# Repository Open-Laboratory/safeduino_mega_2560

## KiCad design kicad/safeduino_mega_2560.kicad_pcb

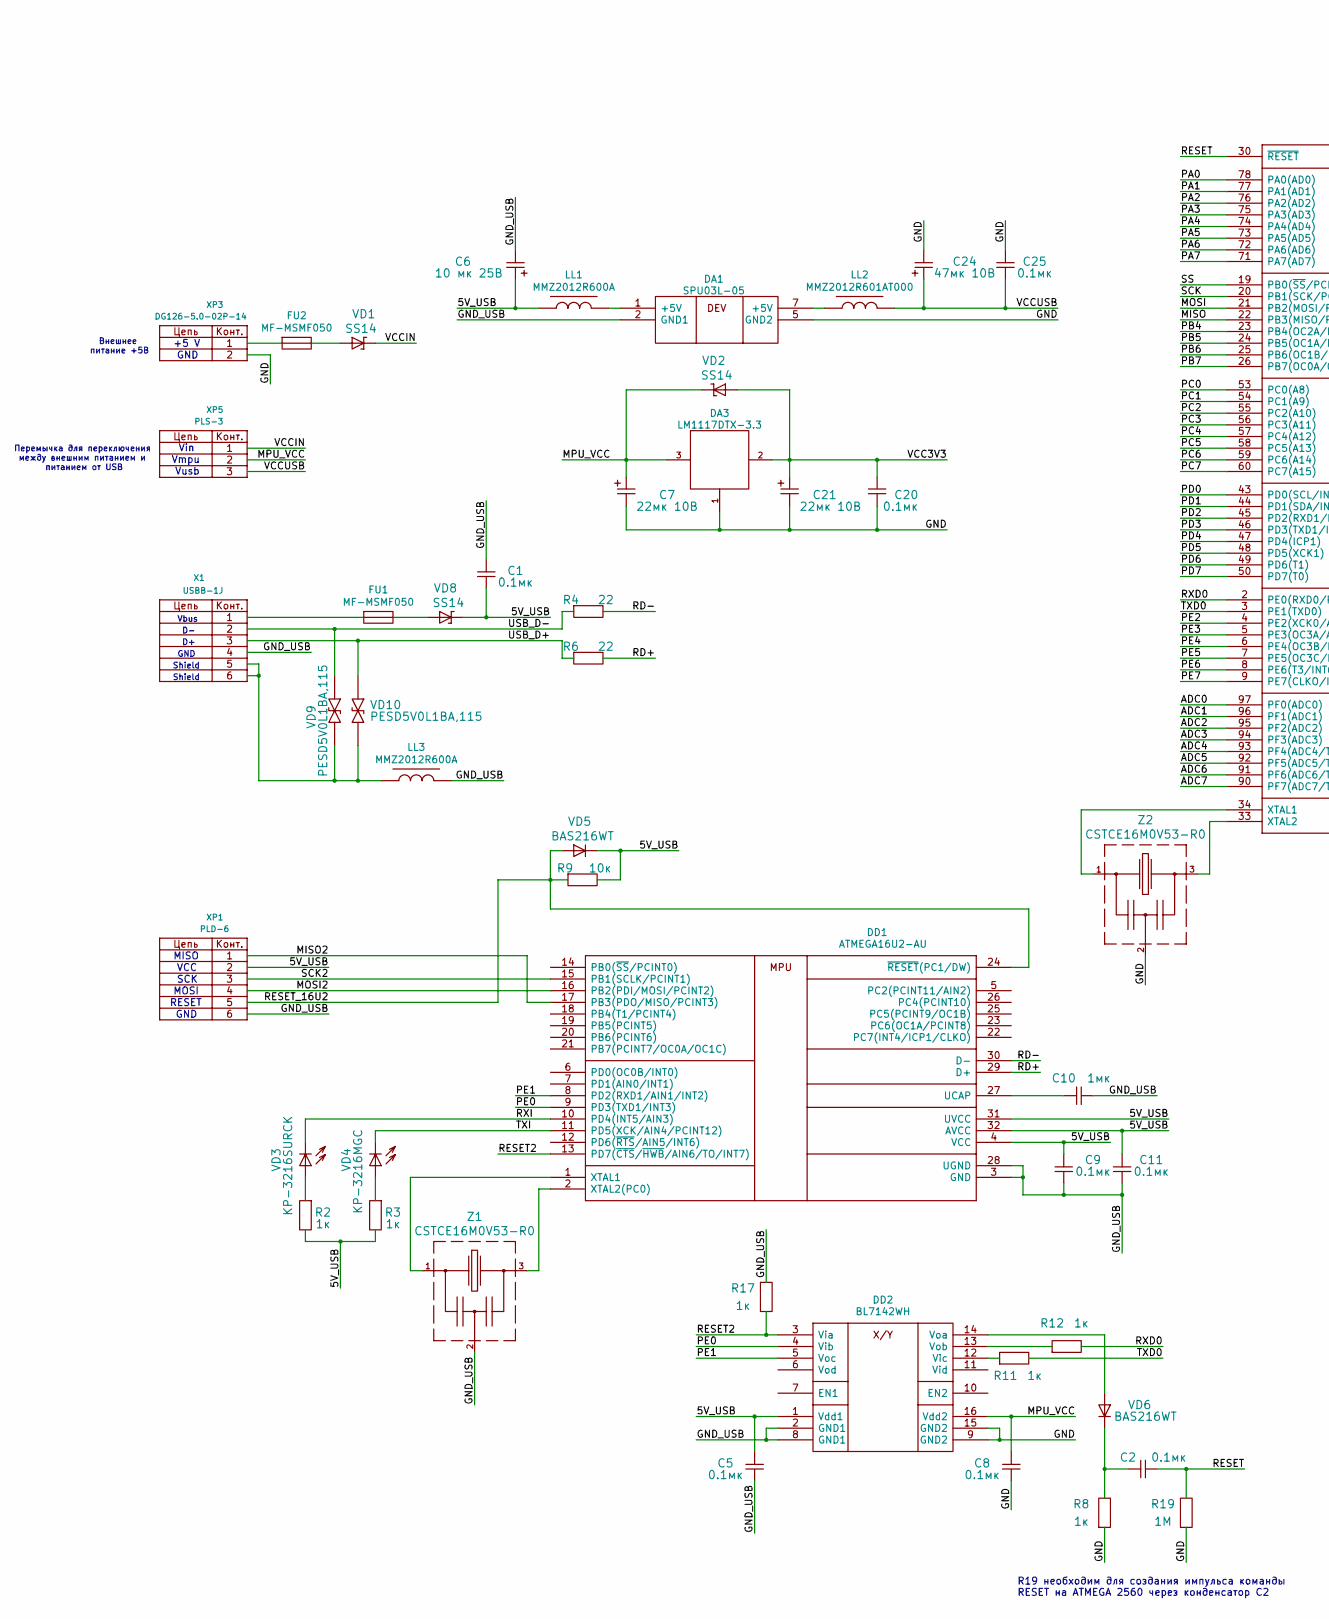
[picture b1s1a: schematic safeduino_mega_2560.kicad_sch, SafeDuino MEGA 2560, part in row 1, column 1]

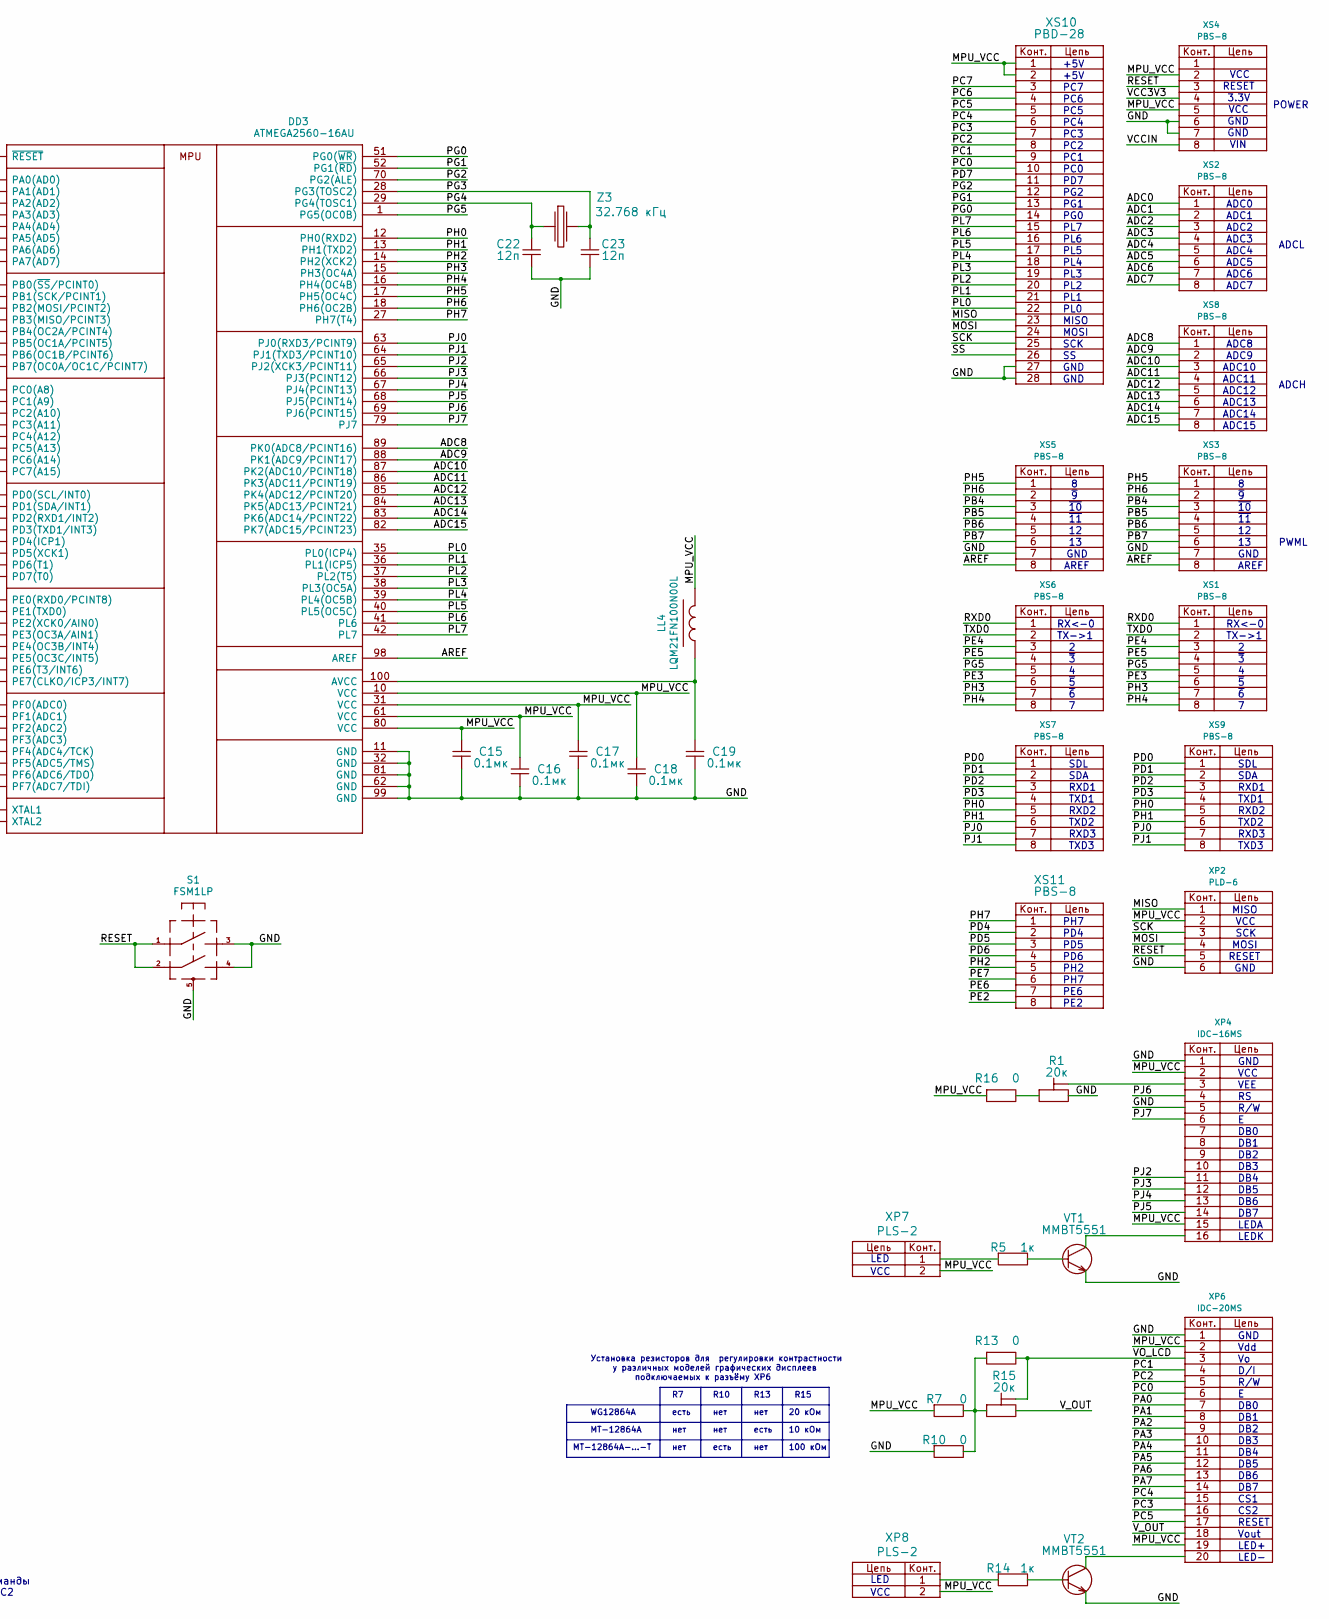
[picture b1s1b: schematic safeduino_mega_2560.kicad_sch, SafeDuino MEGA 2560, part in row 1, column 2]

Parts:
C1, C2, C5, C8, C9, C11, C15, C16, C17, C18, C19, C20, C25: 0.1мк; SMD0603
C6: 10 мк 25В; CASE_C
C7, C21: 22мк 10В; CASE_B
C10: 1мк; SMD0805
C22, C23: 12п; SMD0603
C24: 47мк 10В; CASE_C
DA1: SPU03L-05; SIP-7_4pin
DA3: LM1117DTX-3.3; TO_252
DD1: ATMEGA16U2-AU; TQFP32_case
DD2: BL7142WH; SOIC16_RW16
DD3: ATMEGA2560-16AU; TQFP100_case
FU1, FU2: MF-MSMF050; SMD1812
LL1, LL3: MMZ2012R600A; SMD0805
LL2: MMZ2012R601AT000; SMD0805
LL4: LQM21FN100N00L; SMD0805
R1, R15: 20к; Electron_3296W
R2, R3, R5, R8, R11, R12, R14, R17: 1к; SMD0603
R4, R6: 22; SMD0603
R7, R10, R13, R16: 0; SMD0603
R9: 10к; SMD0603
R19: 1M; SMD0603
S1: FSM1LP; SWD_BUTTON
VD1, VD2, VD8: SS14; SMA
VD3: KP-3216SURCK; LED1206
VD4: KP-3216MGC; LED1206
VD5, VD6: BAS216WT; SOD523
VD9, VD10: PESD5V0L1BA,115; SOD323
VT1, VT2: MMBT5551; SOT_23
X1: USBB-1J; CONN_USB-B
XP1, XP2: PLD-6; PIN_ARRAY_3x2
XP3: DG126-5.0-02P-14
XP4: IDC-16MS
XP5: PLS-3; PIN_ARRAY_3x1
XP6: IDC-20MS
XP7, XP8: PLS-2; PIN_ARRAY_2x1
XS1, XS2, XS3, XS4, XS5, XS6, XS7, XS8, XS9, XS11: PBS-8; PIN_ARRAY_8x1
XS10: PBD-28; PIN_ARRAY_14x2
Z1, Z2: CSTCE16M0V53-R0; CSTNE_G_8-13_99MHz
Z3: 32.768 кГц; SMD0301M2-2

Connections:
/5V_USB: C1.1, C5.2, C6.1, C9.2, C11.2, DD1.4 (VCC), DD1.31 (UVCC), DD1.32 (AVCC), DD2.1 (Vdd1), LL1.2, R2.2, R3.2, R9.2, VD5.2, VD8.2, XP1.2
/ADC0: DD3.97 (PF0(ADC0)), XS2.1
/ADC1: DD3.96 (PF1(ADC1)), XS2.2
/ADC2: DD3.95 (PF2(ADC2)), XS2.3
/ADC3: DD3.94 (PF3(ADC3)), XS2.4
/ADC4: DD3.93 (PF4(ADC4/TCK)), XS2.5
/ADC5: DD3.92 (PF5(ADC5/TMS)), XS2.6
/ADC6: DD3.91 (PF6(ADC6/TDO)), XS2.7
/ADC7: DD3.90 (PF7(ADC7/TDI)), XS2.8
/ADC8: DD3.89 (PK0(ADC8/PCINT16)), XS8.1
/ADC9: DD3.88 (PK1(ADC9/PCINT17)), XS8.2
/ADC10: DD3.87 (PK2(ADC10/PCINT18)), XS8.3
/ADC11: DD3.86 (PK3(ADC11/PCINT19)), XS8.4
/ADC12: DD3.85 (PK4(ADC12/PCINT20)), XS8.5
/ADC13: DD3.84 (PK5(ADC13/PCINT21)), XS8.6
/ADC14: DD3.83 (PK6(ADC14/PCINT22)), XS8.7
/ADC15: DD3.82 (PK7(ADC15/PCINT23)), XS8.8
/AREF: DD3.98 (AREF), XS3.8, XS5.8
/GND: C7.2, C8.1, C15.2, C16.2, C17.2, C18.2, C19.2, C20.2, C21.2, C22.2, C23.2, C24.2, C25.2, DA1.5 (GND2), DA3.1 (com), DD2.9 (GND2), DD2.15 (GND2), DD3.11 (GND), DD3.32 (GND), DD3.62 (GND), DD3.81 (GND), DD3.99 (GND), R1.3, R8.1, R10.1, R19.1, S1.3, S1.4, S1.5, VT1.1, VT2.1, XP2.6, XP3.2, XP4.1, XP4.5, XP6.1, XS3.7, XS4.6, XS4.7, XS5.7, XS10.27, XS10.28, Z2.2
/GND_USB: C1.2, C5.1, C6.2, C9.1, C10.1, C11.1, DA1.2 (GND1), DD1.3 (GND), DD1.28 (UGND), DD2.2 (GND1), DD2.8 (GND1), LL3.1, R17.2, X1.4, XP1.6, Z1.2
/MISO: DD3.22 (PB3(MISO/PCINT3)), XP2.1, XS10.23
/MISO2: DD1.17 (PB3(PDO/MISO/PCINT3)), XP1.1
/MOSI: DD3.21 (PB2(MOSI/PCINT2)), XP2.4, XS10.24
/MOSI2: DD1.16 (PB2(PDI/MOSI/PCINT2)), XP1.4
/MPU_VCC: C7.1, C8.2, C15.1, C16.1, C17.1, C18.1, DA3.3 (Vin), DD2.16 (Vdd2), DD3.10 (VCC), DD3.31 (VCC), DD3.61 (VCC), DD3.80 (VCC), LL4.1, R7.1, R16.1, VD2.2, XP2.2, XP4.2, XP4.15, XP5.2, XP6.2, XP6.19, XP7.2, XP8.2, XS4.2, XS4.5, XS10.1, XS10.2
/PA0: DD3.78 (PA0(AD0)), XP6.7
/PA1: DD3.77 (PA1(AD1)), XP6.8
/PA2: DD3.76 (PA2(AD2)), XP6.9
/PA3: DD3.75 (PA3(AD3)), XP6.10
/PA4: DD3.74 (PA4(AD4)), XP6.11
/PA5: DD3.73 (PA5(AD5)), XP6.12
/PA6: DD3.72 (PA6(AD6)), XP6.13
/PA7: DD3.71 (PA7(AD7)), XP6.14
/PB4: DD3.23 (PB4(OC2A/PCINT4)), XS3.3, XS5.3
/PB5: DD3.24 (PB5(OC1A/PCINT5)), XS3.4, XS5.4
/PB6: DD3.25 (PB6(OC1B/PCINT6)), XS3.5, XS5.5
/PB7: DD3.26 (PB7(OC0A/OC1C/PCINT7)), XS3.6, XS5.6
/PC0: DD3.53 (PC0(A8)), XP6.6, XS10.10
/PC1: DD3.54 (PC1(A9)), XP6.4, XS10.9
/PC2: DD3.55 (PC2(A10)), XP6.5, XS10.8
/PC3: DD3.56 (PC3(A11)), XP6.16, XS10.7
/PC4: DD3.57 (PC4(A12)), XP6.15, XS10.6
/PC5: DD3.58 (PC5(A13)), XP6.17, XS10.5
/PC6: DD3.59 (PC6(A14)), XS10.4
/PC7: DD3.60 (PC7(A15)), XS10.3
/PD0: DD3.43 (PD0(SCL/INT0)), XS7.1, XS9.1
/PD1: DD3.44 (PD1(SDA/INT1)), XS7.2, XS9.2
/PD2: DD3.45 (PD2(RXD1/INT2)), XS7.3, XS9.3
/PD3: DD3.46 (PD3(TXD1/INT3)), XS7.4, XS9.4
/PD4: DD3.47 (PD4(ICP1)), XS11.2
/PD5: DD3.48 (PD5(XCK1)), XS11.3
/PD6: DD3.49 (PD6(T1)), XS11.4
/PD7: DD3.50 (PD7(T0)), XS10.11
/PE0: DD1.9 (PD3(TXD1/INT3)), DD2.4 (Vib)
/PE1: DD1.8 (PD2(RXD1/AIN1/INT2)), DD2.5 (Voc)
/PE2: DD3.4 (PE2(XCK0/AIN0)), XS11.8
/PE3: DD3.5 (PE3(OC3A/AIN1)), XS1.6, XS6.6
/PE4: DD3.6 (PE4(OC3B/INT4)), XS1.3, XS6.3
/PE5: DD3.7 (PE5(OC3C/INT5)), XS1.4, XS6.4
/PE6: DD3.8 (PE6(T3/INT6)), XS11.7
/PE7: DD3.9 (PE7(CLKO/ICP3/INT7)), XS11.6
/PG0: DD3.51 (PG0(~WR)), XS10.14
/PG1: DD3.52 (PG1(~RD)), XS10.13
/PG2: DD3.70 (PG2(ALE)), XS10.12
/PG3: C23.1, DD3.28 (PG3(TOSC2)), Z3.2
/PG4: C22.1, DD3.29 (PG4(TOSC1)), Z3.1
/PG5: DD3.1 (PG5(OC0B)), XS1.5, XS6.5
/PH0: DD3.12 (PH0(RXD2)), XS7.5, XS9.5
/PH1: DD3.13 (PH1(TXD2)), XS7.6, XS9.6
/PH2: DD3.14 (PH2(XCK2)), XS11.5
/PH3: DD3.15 (PH3(OC4A)), XS1.7, XS6.7
/PH4: DD3.16 (PH4(OC4B)), XS1.8, XS6.8
/PH5: DD3.17 (PH5(OC4C)), XS3.1, XS5.1
/PH6: DD3.18 (PH6(OC2B)), XS3.2, XS5.2
/PH7: DD3.27 (PH7(T4)), XS11.1
/PJ0: DD3.63 (PJ0(RXD3/PCINT9)), XS7.7, XS9.7
/PJ1: DD3.64 (PJ1(TXD3/PCINT10)), XS7.8, XS9.8
/PJ2: DD3.65 (PJ2(XCK3/PCINT11)), XP4.11
/PJ3: DD3.66 (PJ3(PCINT12)), XP4.12
/PJ4: DD3.67 (PJ4(PCINT13)), XP4.13
/PJ5: DD3.68 (PJ5(PCINT14)), XP4.14
/PJ6: DD3.69 (PJ6(PCINT15)), XP4.4
/PJ7: DD3.79 (PJ7), XP4.6
/PL0: DD3.35 (PL0(ICP4)), XS10.22
/PL1: DD3.36 (PL1(ICP5)), XS10.21
/PL2: DD3.37 (PL2(T5)), XS10.20
/PL3: DD3.38 (PL3(OC5A)), XS10.19
/PL4: DD3.39 (PL4(OC5B)), XS10.18
/PL5: DD3.40 (PL5(OC5C)), XS10.17
/PL6: DD3.41 (PL6), XS10.16
/PL7: DD3.42 (PL7), XS10.15
/RD+: DD1.29 (D+), R6.2
/RD-: DD1.30 (D-), R4.2
/RESET: C2.1, DD3.30 (~RESET), R19.2, S1.1, S1.2, XP2.5, XS4.3
/RESET2: DD1.13 (PD7(~CTS/~HWB/AIN6/TO/INT7)), DD2.3 (Via), R17.1
/RESET_16U2: DD1.24 (~RESET(PC1/DW)), R9.1, VD5.1, XP1.5
/RXD0: DD3.2 (PE0(RXD0/PCINT8)), R12.2, XS1.1, XS6.1
/RXI: DD1.10 (PD4(INT5/AIN3)), VD3.2
/SCK: DD3.20 (PB1(SCK/PCINT1)), XP2.3, XS10.25
/SCK2: DD1.15 (PB1(SCLK/PCINT1)), XP1.3
/SS: DD3.19 (PB0(~SS/PCINT0)), XS10.26
/TXD0: DD3.3 (PE1(TXD0)), R11.2, XS1.2, XS6.2
/TXI: DD1.11 (PD5(XCK/AIN4/PCINT12)), VD4.2
/USB_D+: R6.1, VD10.1, X1.3
/USB_D-: R4.1, VD9.1, X1.2
/VCC3V3: C20.1, C21.1, DA3.2 (Vout), VD2.1, XS4.4
/VCCIN: VD1.2, XP5.1, XS4.8
/VCCUSB: C24.1, C25.1, LL2.1, XP5.3
/VO_LCD: R13.2, R15.2, XP6.3
/V_OUT: R15.3, XP6.18
unnamed: C2.2, R8.2, VD6.2
unnamed: DA1.1 (+5V), LL1.1
unnamed: DA1.7 (+5V), LL2.2
unnamed: C10.2, DD1.27 (UCAP)
unnamed: DD1.1 (XTAL1), Z1.1
unnamed: DD1.2 (XTAL2(PC0)), Z1.3
unnamed: DD2.12 (Vic), R11.1
unnamed: DD2.14 (Voa), VD6.1
unnamed: DD2.13 (Vob), R12.1
unnamed: C19.1, DD3.100 (AVCC), LL4.2
unnamed: DD3.34 (XTAL1), Z2.1
unnamed: DD3.33 (XTAL2), Z2.3
unnamed: FU1.1, X1.1
unnamed: FU1.2, VD8.1
unnamed: FU2.1, XP3.1
unnamed: FU2.2, VD1.1
unnamed: LL3.2, VD9.2, VD10.2, X1.5, X1.6
unnamed: R1.1, R16.2
unnamed: R1.2, XP4.3
unnamed: R2.1, VD3.1
unnamed: R3.1, VD4.1
unnamed: R5.1, XP7.1
unnamed: R5.2, VT1.2
unnamed: R7.2, R10.2, R13.1, R15.1
unnamed: R14.1, XP8.1
unnamed: R14.2, VT2.2
unnamed: VT1.3, XP4.16
unnamed: VT2.3, XP6.20

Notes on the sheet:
TXD3
DB4
PG1
PC7
RESET
MOSI
TXD1
Shield
POWER
GND
есть
VCC
~{10}
ADC10
PC5
ADC11
RXD3
+5 V
ADC2
PH2
PD7
DB2
ADC1
PG2
Внешнее питание +5В
D/I
ADC15
PH7
DB1
RXD2
CS1
LEDA
PL4
ADC5
ADC8
PWML
CS2
~{6}
Vout
SCK

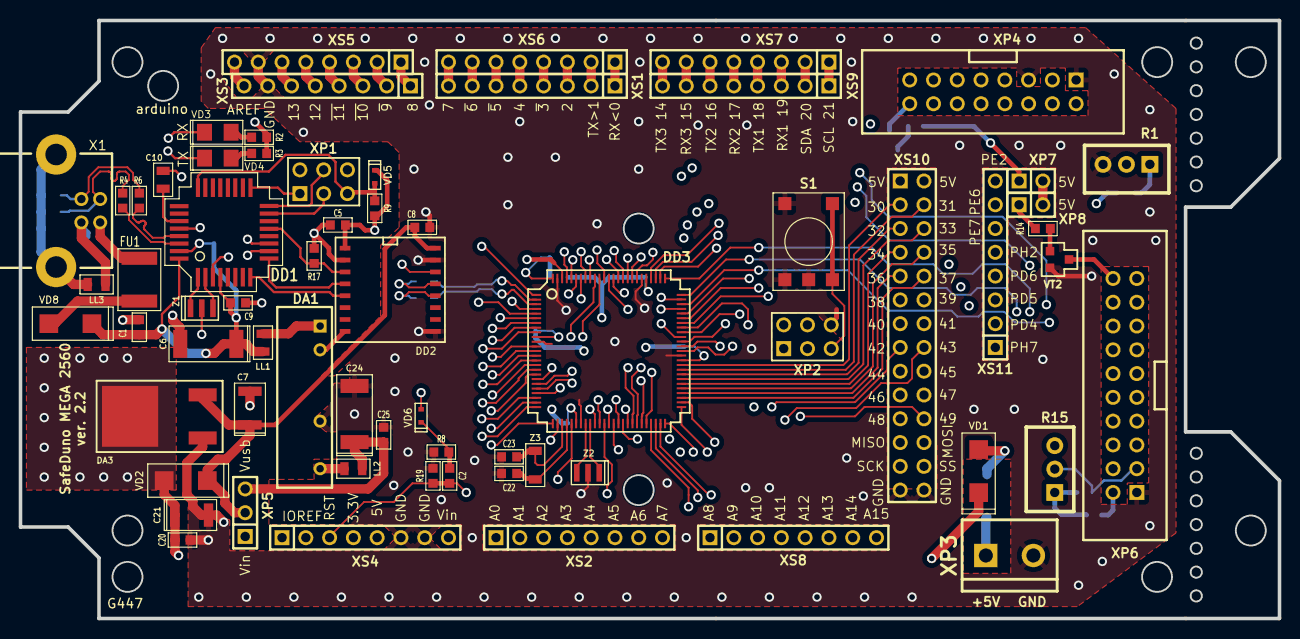
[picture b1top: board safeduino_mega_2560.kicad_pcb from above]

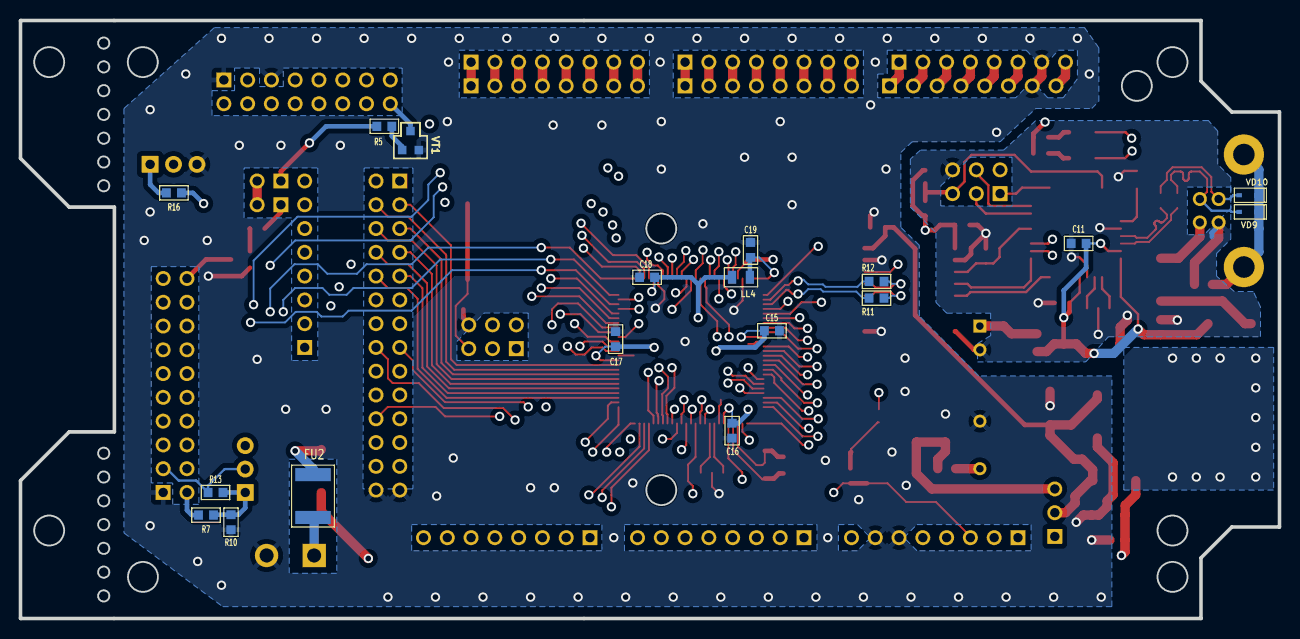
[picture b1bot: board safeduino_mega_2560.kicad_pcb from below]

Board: 4 copper layers, 134.5 x 63.9 mm, 84 parts (18 on the bottom side), 138 nets.

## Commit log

2015-03-30 -aДобавил печатную плату SafeDuino MEGA 2560.
2015-03-30 added kicad components
2015-04-06 Исправил ошибку в подключении ADUM1301.
2015-04-15 Исправил ошибку с сигналом RESER.
2015-04-16 Услучшил разводку платы SafeDuino MEGA 2560.
2015-04-24 Поправил ошибку с перевёрнутым разъёмом.
2015-10-08 Исправил неточности в схеме.
2015-11-05 Поправил шелкографию и посадочное место для кнопки Reset.
2016-03-10 Заменил резистор R16 на диод для защиты ADUM от попадания напряжения на входную ногу.
2021-09-09 Приступил к разработке новой ревизии платы SafeDuino MEGA 2560 ver. 1.1.
2021-09-09 Удалил из проекта лишние файлы.
2021-09-13 Продолжил переделывать проект.
2022-11-17 Приступил к переработке платы SafeDuino MEGA 2560.
2022-11-18 Продолжил переделывать SafeDuino MEGA 2560.
2022-12-06 Продолжил переделывать печатную плату SafeDuino MEGA 2560.
2022-12-09 Продолжил трассировку печатной платы SafeDuino MEGA 2560.
2022-12-12 Закончил предварительную трассировку платы SafeDuino MEGA 2560.
2022-12-13 Оптимизировал трассировку печатной платы.
2022-12-14 Продолжил оптимизацию трассировки печатной платы.
2022-12-15 Поправил схему для лучшей защиты от ЭМП и продолжил переделывать трассировку печатной платы.
2022-12-16 Продолжил оптимизировать трассировку печатной платы.
2022-12-22 Закончил предварительную трассировку платы.
2022-12-23 Добавил в схему различные варианты подключения резистора регулировки контрастности для графического дисплея.
2023-01-18 Сохранил проект печатной платы в KiCad 6.0.2. и исправил недочёты в трассировке.
2023-01-23 Убрал старые версии файлов и добавил новые для Kicad 6.0.2.
2023-02-06 Добавил схему BL7142WH для сравнения с ADUM1301.
2023-02-07 Заменил посадочные места на SOD523 у VD5 и VD6.
2023-02-22 Отправил печатную плату в производство.
2023-02-28 Добавил в файл с настройками (*.kicad_prl).
2023-06-15 Поправил ошибку с размерами разъёма USB-B и расположение компонентов около него, которые могли вызвать КЗ.
2023-12-26 Перевёл проект SafeDuino MEGA 2560 на Kicad 7.0 и поправил найденные недочёты на печатной плате.
